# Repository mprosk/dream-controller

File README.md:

# dream-controller
Joycon meets Steam Controller

Nintendo Switch hack that replaces the joystick with a capacitive touchpad. Includes USB HID mouse emulation.
Inspired by [Matteo Pisani](https://medium.com/@matteo.pisani.91/how-i-hacked-nintendo-joy-con-controller-8ac22d75b0b8)

| Component              | Description                 | Link                                                         |
| ---------------------- | --------------------------- | ------------------------------------------------------------ |
| Cirque Glidepoint 23mm | Capacitive touch sensor     | [Mouser](https://www.mouser.com/ProductDetail/Cirque/TM023023-2024-000?qs=sGAEpiMZZMv0NwlthflBi9N1a4ghWNXsADUFmDElQZ8%3D) |
| MCP4922                | Digital to analog converter | [Mouser](https://www.mouser.com/ProductDetail/Microchip-Technology/MCP4922-E-ST?qs=iRhCjdSJZe6gRerFwLixKQ%3D%3D) |
| Teensy LC              | Microcontroller             | [PJRC](https://www.pjrc.com/store/teensylc.html)             |
| FFC Cable              | 12 pin 0.5mm pitch          | [Mouser](https://www.mouser.com/c/connectors/ffc-fpc/ffc-fpc-jumper-cables/?number%20of%20conductors=12%20Conductor&pitch=0.5%20mm&instock=y&sort=pricing) |
| FFC Connector          | 12 pin 0.5mm pitch          | [Mouser](https://www.mouser.com/ProductDetail/Amphenol-Aorora/F31K-1A7H1-11012?qs=xZ%2FP%252Ba9zWqZ7VOcLJC0XAg%3D%3D) |

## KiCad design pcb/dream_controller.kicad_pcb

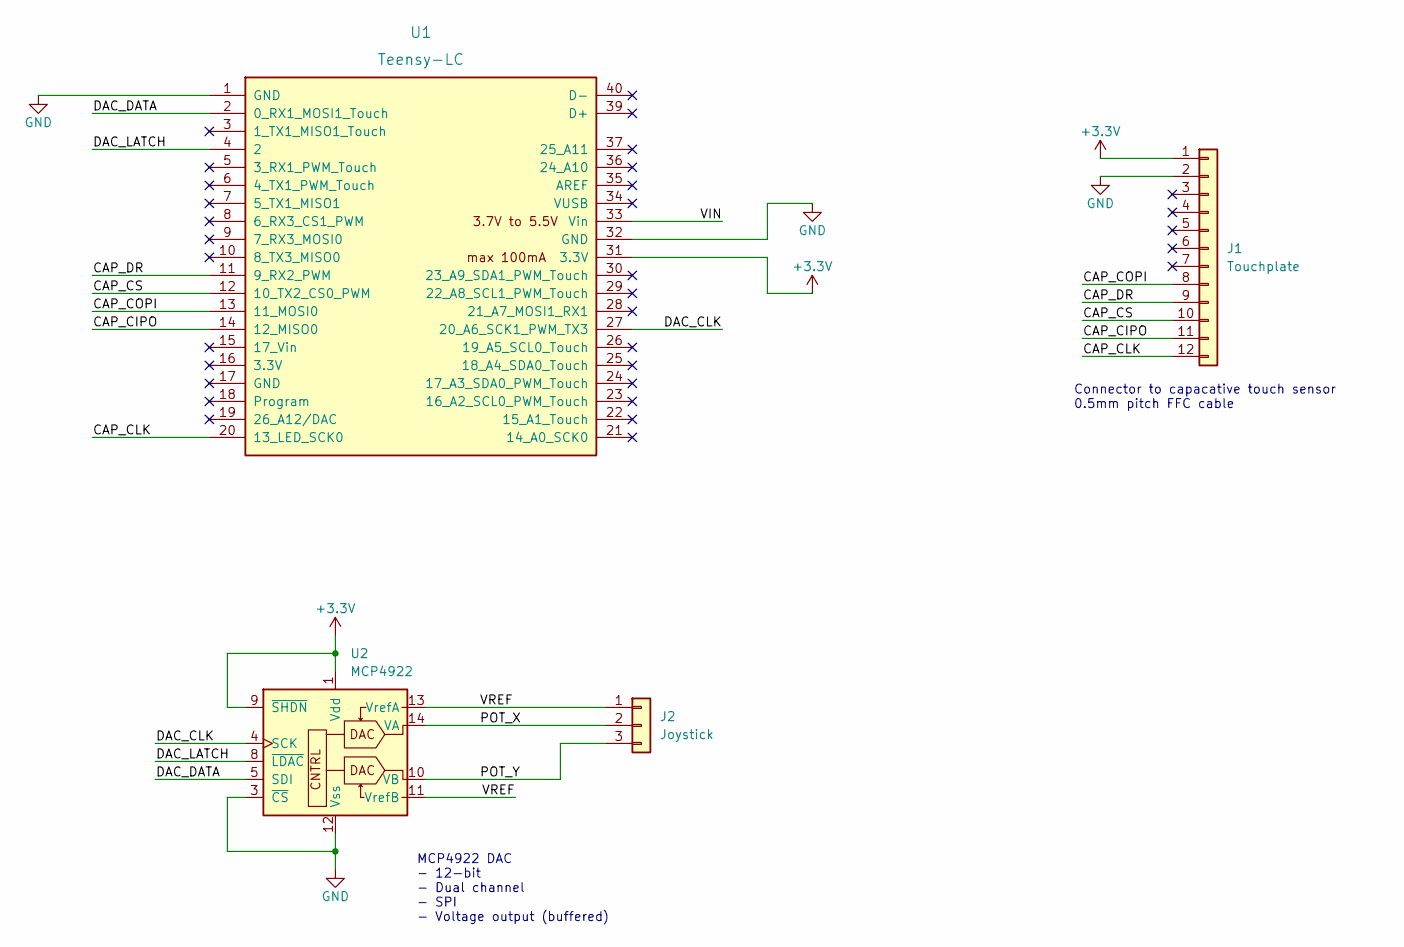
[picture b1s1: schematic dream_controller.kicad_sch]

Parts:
J1: Touchplate; TE Connectivity 12P0.5mm FPC
J2: Joystick; PinHeader_1x03_P2.00mm_Vertical
U1: Teensy-LC; Teensy_LC
U2: MCP4922; TSSOP-14_4.4x5mm_P0.65mm

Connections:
+3V3: J1.1, U1.31 (3.3V), U2.1 (Vdd), U2.9 (~SHDN)
/CAP_CIPO: J1.11, U1.14 (12_MISO0)
/CAP_CLK: J1.12, U1.20 (13_LED_SCK0)
/CAP_COPI: J1.8, U1.13 (11_MOSI0)
/CAP_CS: J1.10, U1.12 (10_TX2_CS0_PWM)
/CAP_DR: J1.9, U1.11 (9_RX2_PWM)
/DAC_CLK: U1.27 (20_A6_SCK1_PWM_TX3), U2.4 (SCK)
/DAC_DATA: U1.2 (0_RX1_MOSI1_Touch), U2.5 (SDI)
/DAC_LATCH: U1.4 (2), U2.8 (~LDAC)
/POT_X: J2.2, U2.14 (VA)
/POT_Y: J2.3, U2.10 (VB)
/VIN: U1.33 (Vin)
/VREF: J2.1, U2.11 (VrefB), U2.13 (VrefA)
GND: J1.2, U1.1 (GND), U1.32 (GND), U2.3 (~CS), U2.12 (Vss)

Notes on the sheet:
MCP4922 DAC - 12-bit - Dual channel - SPI - Voltage output (buffered)
Connector to capacative touch sensor 0.5mm pitch FFC cable

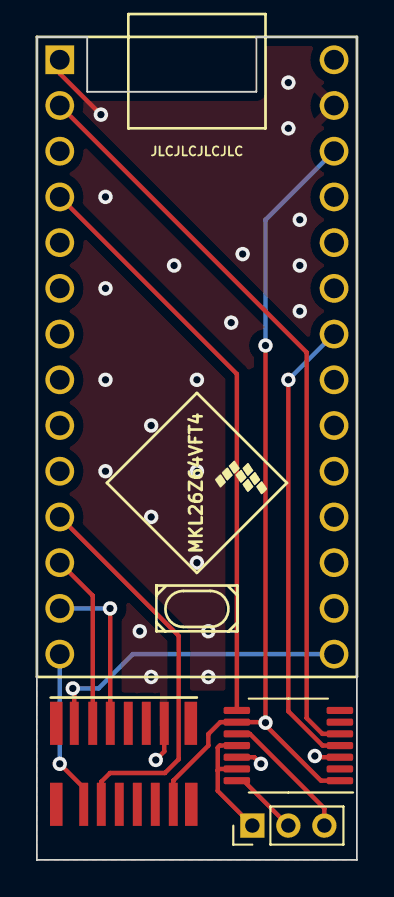
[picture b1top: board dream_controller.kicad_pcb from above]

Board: 2 copper layers, 17.8 x 45.7 mm, 4 parts (0 on the bottom side), 13 nets.

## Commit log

2022-03-03 Add HID mouse experimental code
2022-03-03 Move pinnacle shit to its own header file
2022-03-04 Make the mouse a bit more sensitive
2022-03-09 Add KiCAD project stub
2022-03-10 Get proof of concept DAC output going
2022-03-10 Add info on DAC and connectors
2022-03-15 nitial schematic
2022-03-15 Clean up schematic
2022-03-15 Remove backups from git repo
2022-03-15 Add backups folder to gitignore
2022-03-18 uwu pogchamp
2022-03-18 Complete schematic
2022-03-18 Cleanup
2022-03-21 Update readme with final parts
2022-03-30 Additional cleanup
2022-03-30 silkscreen name
2022-03-30 Merge working branch to main (#1)
    * Complete schematic
    * Cleanup
    * Additional cleanup
    * silkscreen name
2022-04-09 Get DAC working
2022-05-03 Add button and LED behavior to controller
2022-05-03 Dont output mouse when in stick mode. Remove serial printout
